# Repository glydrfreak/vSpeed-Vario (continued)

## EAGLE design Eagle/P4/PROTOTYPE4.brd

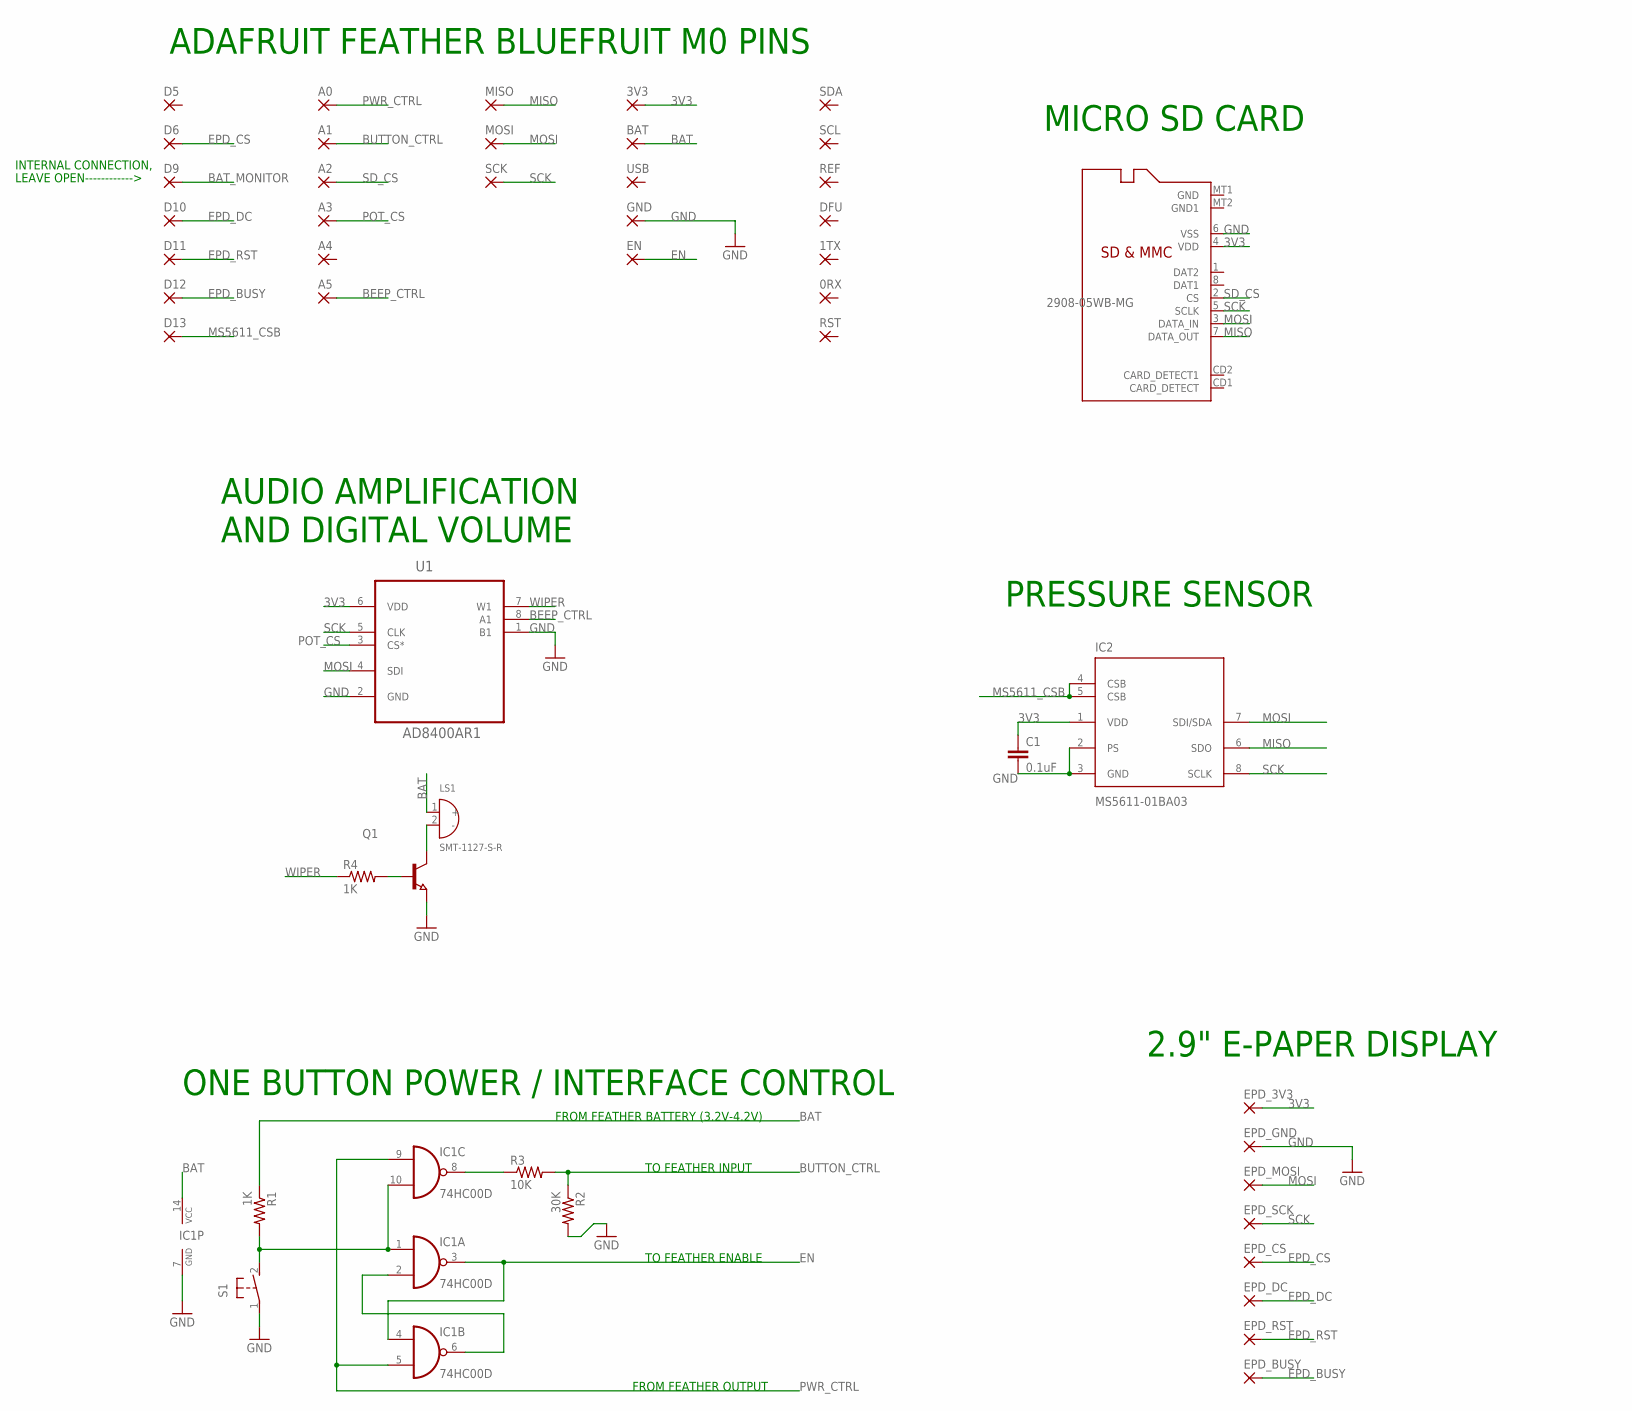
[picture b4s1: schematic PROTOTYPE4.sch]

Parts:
0RX, 1TX, 3V3: SMD2; SMD1,27-2,54
A0, A1, A2, A3, A4, A5: SMD2; SMD1,27-2,54
BAT: SMD2; SMD1,27-2,54
C1: 0.1uF; C0805K
D5, D6, D9, D10, D11, D12, D13: SMD2; SMD1,27-2,54
DFU: SMD2; SMD1,27-2,54
EN: SMD2; SMD1,27-2,54
EPD_3V3: SMD2; SMD1,27-2,54
EPD_BUSY: SMD2; SMD1,27-2,54
EPD_CS: SMD2; SMD1,27-2,54
EPD_DC: SMD2; SMD1,27-2,54
EPD_GND: SMD2; SMD1,27-2,54
EPD_MOSI: SMD2; SMD1,27-2,54
EPD_RST: SMD2; SMD1,27-2,54
EPD_SCK: SMD2; SMD1,27-2,54
GND: SMD2; SMD1,27-2,54
IC1: 74HC00D; SO14
IC2: MS5611-01BA03; SON125P300X500X100-8N
LS1: SMT-1127-S-R; XDCR_SMT-1127-S-R
MISO: SMD2; SMD1,27-2,54
MOSI: SMD2; SMD1,27-2,54
Q1: NPN-TRANSISTOR_SOT23; SOT23
R1, R4: 1K; R0805
R2: 30K; R0805
R3: 10K; R0805
REF: SMD2; SMD1,27-2,54
RST: SMD2; SMD1,27-2,54
S1: 31-XX; B3F-31XX; MPN B3F-3120
SCK: SMD2; SMD1,27-2,54
SCL: SMD2; SMD1,27-2,54
SDA: SMD2; SMD1,27-2,54
U1: AD8400AR1; SOIC127P600X175-8N
U$1: 2908-05WB-MG; MICROSD
USB: SMD2; SMD1,27-2,54

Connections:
3V3: 3V3.1, C1.1, EPD_3V3.1, IC2.1 (VDD), U1.6 (VDD), U$1.4 (VDD)
BAT: BAT.1, IC1.14 (VCC), LS1.1 (+), R1.1
BAT_MONITOR: D9.1
BEEP_CTRL: A5.1, U1.8 (A1)
BUTTON_CTRL: A1.1, R2.1, R3.2
EN: EN.1, IC1.3 (O), IC1.4 (I0)
EPD_BUSY: D12.1, EPD_BUSY.1
EPD_CS: D6.1, EPD_CS.1
EPD_DC: D10.1, EPD_DC.1
EPD_RST: D11.1, EPD_RST.1
GND: C1.2, EPD_GND.1, GND.1, IC1.7 (GND), IC2.2 (PS), IC2.3 (GND), Q1.2 (E), R2.2, S1.1, U1.1 (B1), U1.2 (GND), U$1.6 (VSS)
MISO: IC2.6 (SDO), MISO.1, U$1.7 (DATA_OUT)
MOSI: EPD_MOSI.1, IC2.7 (SDI/SDA), MOSI.1, U1.4 (SDI), U$1.3 (DATA_IN)
MS5611_CSB: D13.1, IC2.4 (CSB), IC2.5 (CSB)
unnamed: IC1.1 (I0), IC1.10 (I1), R1.2, S1.2 (S)
unnamed: IC1.2 (I1), IC1.6 (O)
unnamed: IC1.8 (O), R3.1
unnamed: Q1.1 (B), R4.2
unnamed: LS1.2 (-), Q1.3 (C)
POT_CS: A3.1, U1.3 (CS*)
PWR_CTRL: A0.1, IC1.5 (I1), IC1.9 (I0)
SCK: EPD_SCK.1, IC2.8 (SCLK), SCK.1, U1.5 (CLK), U$1.5 (SCLK)
SD_CS: A2.1, U$1.2 (CS)
WIPER: R4.1, U1.7 (W1)

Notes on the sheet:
TO FEATHER INPUT
TO FEATHER ENABLE
FROM FEATHER OUTPUT
FROM FEATHER BATTERY (3.2V-4.2V)
ADAFRUIT FEATHER BLUEFRUIT M0 PINS
ONE BUTTON POWER / INTERFACE CONTROL
MICRO SD CARD
PRESSURE SENSOR
AUDIO AMPLIFICATION AND DIGITAL VOLUME
2.9" E-PAPER DISPLAY
LEAVE OPEN------------>
INTERNAL CONNECTION,

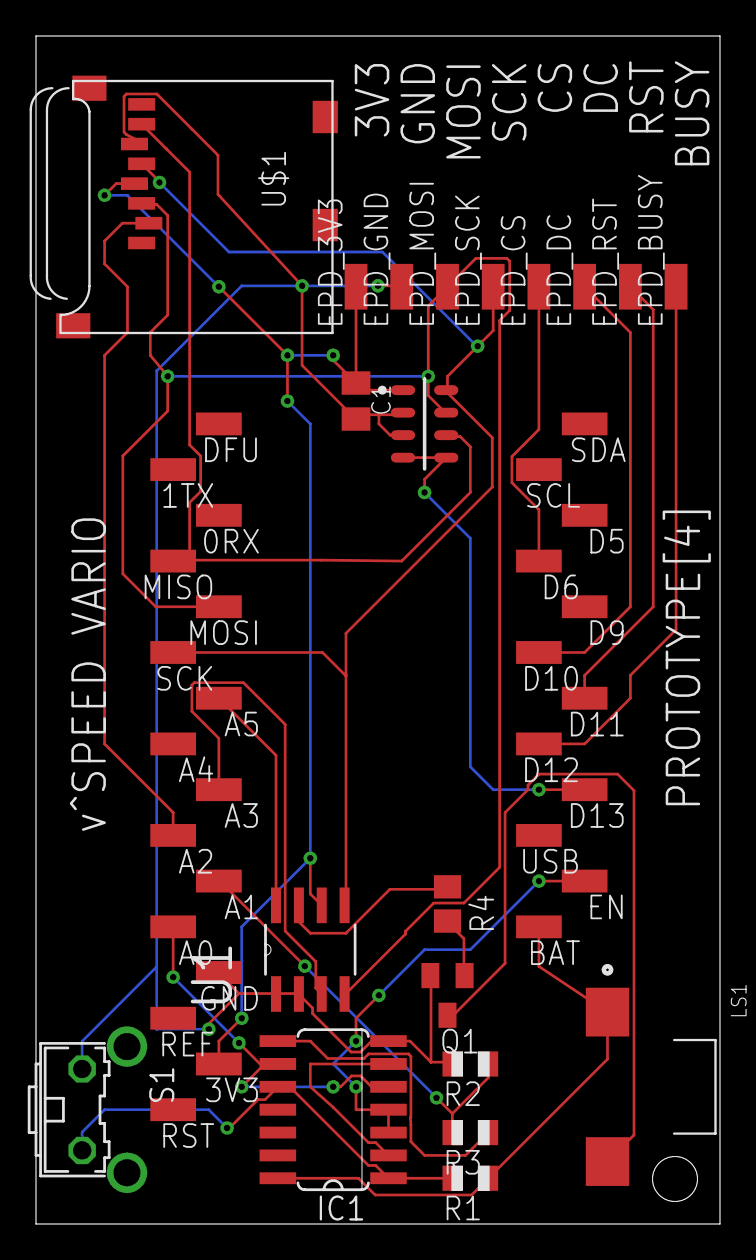
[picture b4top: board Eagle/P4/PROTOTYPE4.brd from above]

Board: 2 copper layers, 38.0 x 66.0 mm, 48 parts (0 on the bottom side), 23 nets.

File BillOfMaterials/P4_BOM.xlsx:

| PROTOTYPE[4]
 | Designator | Manufacturer Part Number | QTY | DESCRIPTION |  | DISTRIBUTER | DIVIDED PRICE | INCLUDED |  | DISTRIBUTER | DIVIDED PRICE | INCLUDED |  |  | DISTRIBUTER | EXTENDED PRICE | INCLUDED
 | R2 | RC0805FR-0730KL | 1 | RES 30K |  | DIGIKEY | 0.1 | 1 |  | DIGIKEY | 2.1999999999999999E-2 | 10 |  |  | DIGIKEY | 0.88 | 100
 | IC1 | 74HC00D,652 | 1 | NAND |  | DIGIKEY | 0.36 | 1 |  | DIGIKEY | 0.28999999999999998 | 10 |  |  | DIGIKEY | 19.739999999999998 | 100
 | C1 | 08055C104JAT2A | 1 | CAP 0.1UF |  | DIGIKEY | 0.1 | 1 |  | DIGIKEY | 7.0000000000000007E-2 | 10 |  |  | DIGIKEY | 3.1 | 100
 | R3 | RC0805JR-0710KL | 1 | RES 10K |  | DIGIKEY | 0.1 | 1 |  | DIGIKEY | 1.9E-2 | 10 |  |  | DIGIKEY | 0.76 | 100
 | R1,R4 | RC0805JR-071KL | 2 | RES 1K |  | DIGIKEY | 0.19 | 10 |  | DIGIKEY | 1.9E-2 | 20 |  |  | DIGIKEY | 1.52 | 200
 | U$1 | 2908-05WB-MG | 1 | SD |  | DIGIKEY | 3.6 | 1 |  | DIGIKEY | 3.4580000000000002 | 10 |  |  | DIGIKEY | 288.2 | 100
 | U1 | AD8400ARZ1 | 1 | SPI POT 1K |  | DIGIKEY | 3.31 | 1 |  | DIGIKEY | 3.31 | 10 |  |  | DIGIKEY | 281.255 | 100
 | Q1 | MMBT2222ALT1G | 1 | NPN TRANSISTOR |  | DIGIKEY | 0.12 | 1 |  | DIGIKEY | 0.106 | 10 |  |  | DIGIKEY | 5.75 | 100
 | S1 | B3F-3120 | 1 | BUTTON |  | DIGIKEY | 0.44 | 1 |  | DIGIKEY | 0.42399999999999999 | 10 |  |  | DIGIKEY | 34.520000000000003 | 100
 | DFU,MOSI,A3,GND,SDA,D9,D13 | 878980426 | 7 | VERT HEADER |  | DIGIKEY | 2.5300000000000002 | 10 |  | DIGIKEY | 1.77 | 100 |  |  | DIGIKEY | 106.134 | 700
 | EPD_3V3 | GEC08SBSN-M89 | 1 | RA HEADER |  | DIGIKEY | 1.53 | 1 |  | DIGIKEY | 1.367 | 10 |  |  | DIGIKEY | 112.6 | 100
 |  | ESTIMATED DIGIKEY SHIPPING | 1 | SHIPPING |  | SHIPPING | 3.69 | 1 |  | SHIPPING | 0.36899999999999999 | 10 |  |  | SHIPPING | 3.69 | 100
 | IC2 | MS561101BA03-50 | 1 | SENSOR |  | EBAY | 5.58 | 1 |  | EBAY | 5.58 | 10 |  |  | EBAY | 558 | 100
 | LS1 | BOT-03D-BUJEON, SMT-1127-S-R (ALT) | 1 | BUZZER |  | EBAY | 3.61 | 10 |  | EBAY | 0.36099999999999999 | 10 |  |  | EBAY | 36.1 | 100
 |  | 2.9 INCH E-PAPER MODULE WITH WIRES | 1 | EPAPER |  | EBAY | 18.760000000000002 | 1 |  | EBAY | 18.752000000000002 | 10 |  |  | EBAY | 1875.2 | 100
 |  | SOLDER PASTE | ? | SOLDER PASTE |  | EBAY | UNKNOWN |  |  | EBAY | UNKNOWN |  |  |  | EBAY | UNKNOWN
 |  | ESTIMATED EBAY SHIPPING | 1 | SHIPPING |  | SHIPPING | 3.18 | 1 |  | SHIPPING | 1.2310000000000001 | 10 |  |  | SHIPPING | 113.85000000000001 | 100
 |  | BLUEFRUIT FEATHER M0 | 1 | CONTROLLER |  | ADAFRUIT | 29.95 | 1 |  | ADAFRUIT | 26.96 | 10 |  |  | ADAFRUIT | 2396 | 100
 |  | FEMALE HEADER SOCKETS 12 AND 16 PIN | 1 | SOCKET |  | ADAFRUIT | 0.95 | 1 |  | ADAFRUIT | 0.86 | 10 |  |  | ADAFRUIT | 76 | 100
 |  | ADAFRUIT SHIPPING | 1 | SHIPPING |  | SHIPPING | 4.05 | 1 |  | ADAFRUIT | FREE | 10 |  |  | ADAFRUIT | FREE | 100
 |  | BTG 150mAh LIPO BATTERY | 1 | BATTERY |  | AMAZON | 12.85 | 5 |  | AMAZON | 2.57 | 10 |  |  | AMAZON | 257 | 100
 |  | FREE SHIPPING WITH AMAZON PRIME | 1 | SHIPPING |  | SHIPPING | FREE | 5 |  | SHIPPING | FREE | 10 |  |  | SHIPPING | FREE | 100
 |  | PCB | 1 | EAGLE CAD |  | SEEED | 4.9000000000000004 | 5 |  | SEEED | 0.49000000000000005 | 10 |  |  | SEEED | 41.59 | 100
 |  | SEEED STUDIO SHIPPING | 1 | SHIPPING |  | SHIPPING | 10.85 | 5 |  | SEEED | 1.1139999999999999 | 10 |  |  | SEEED | 17.55 | 100
 |  | SOLDER STENCIL | 1 | HOME 3D PRINTED |  | PRUSA MK3 | UNKNOWN | 1 |  | PRUSA MK3 | UNKNOWN | 10 |  |  | PRUSA MK3 | UNKNOWN | 100
 |  | CASE (THREE PIECES TOTAL) | 1 | HOME 3D PRINTED |  | PRUSA MK3 | UNKNOWN | 1 |  | PRUSA MK3 | UNKNOWN | 10 |  |  | PRUSA MK3 | UNKNOWN | 100
 |  | ASSUMING YOU HAVE YOUR OWN PRINTER | 1 | SHIPPING |  | SHIPPING | FREE |  |  | SHIPPING | FREE |  |  |  | SHIPPING | FREE
 |  |  |  |  |  | TOTAL PURCHASE | 110.74999999999999 |  |  | TOTAL PURCHASE | 691.42 |  |  |  | TOTAL PURCHASE | 6229.4389999999994
 |  |  |  |  |  | 1 VARIO | 110.74999999999999 | EACH |  | 10 VARIOS | 69.141999999999996 | EACH |  |  | 100 VARIOS | 62.294389999999993 | EACH

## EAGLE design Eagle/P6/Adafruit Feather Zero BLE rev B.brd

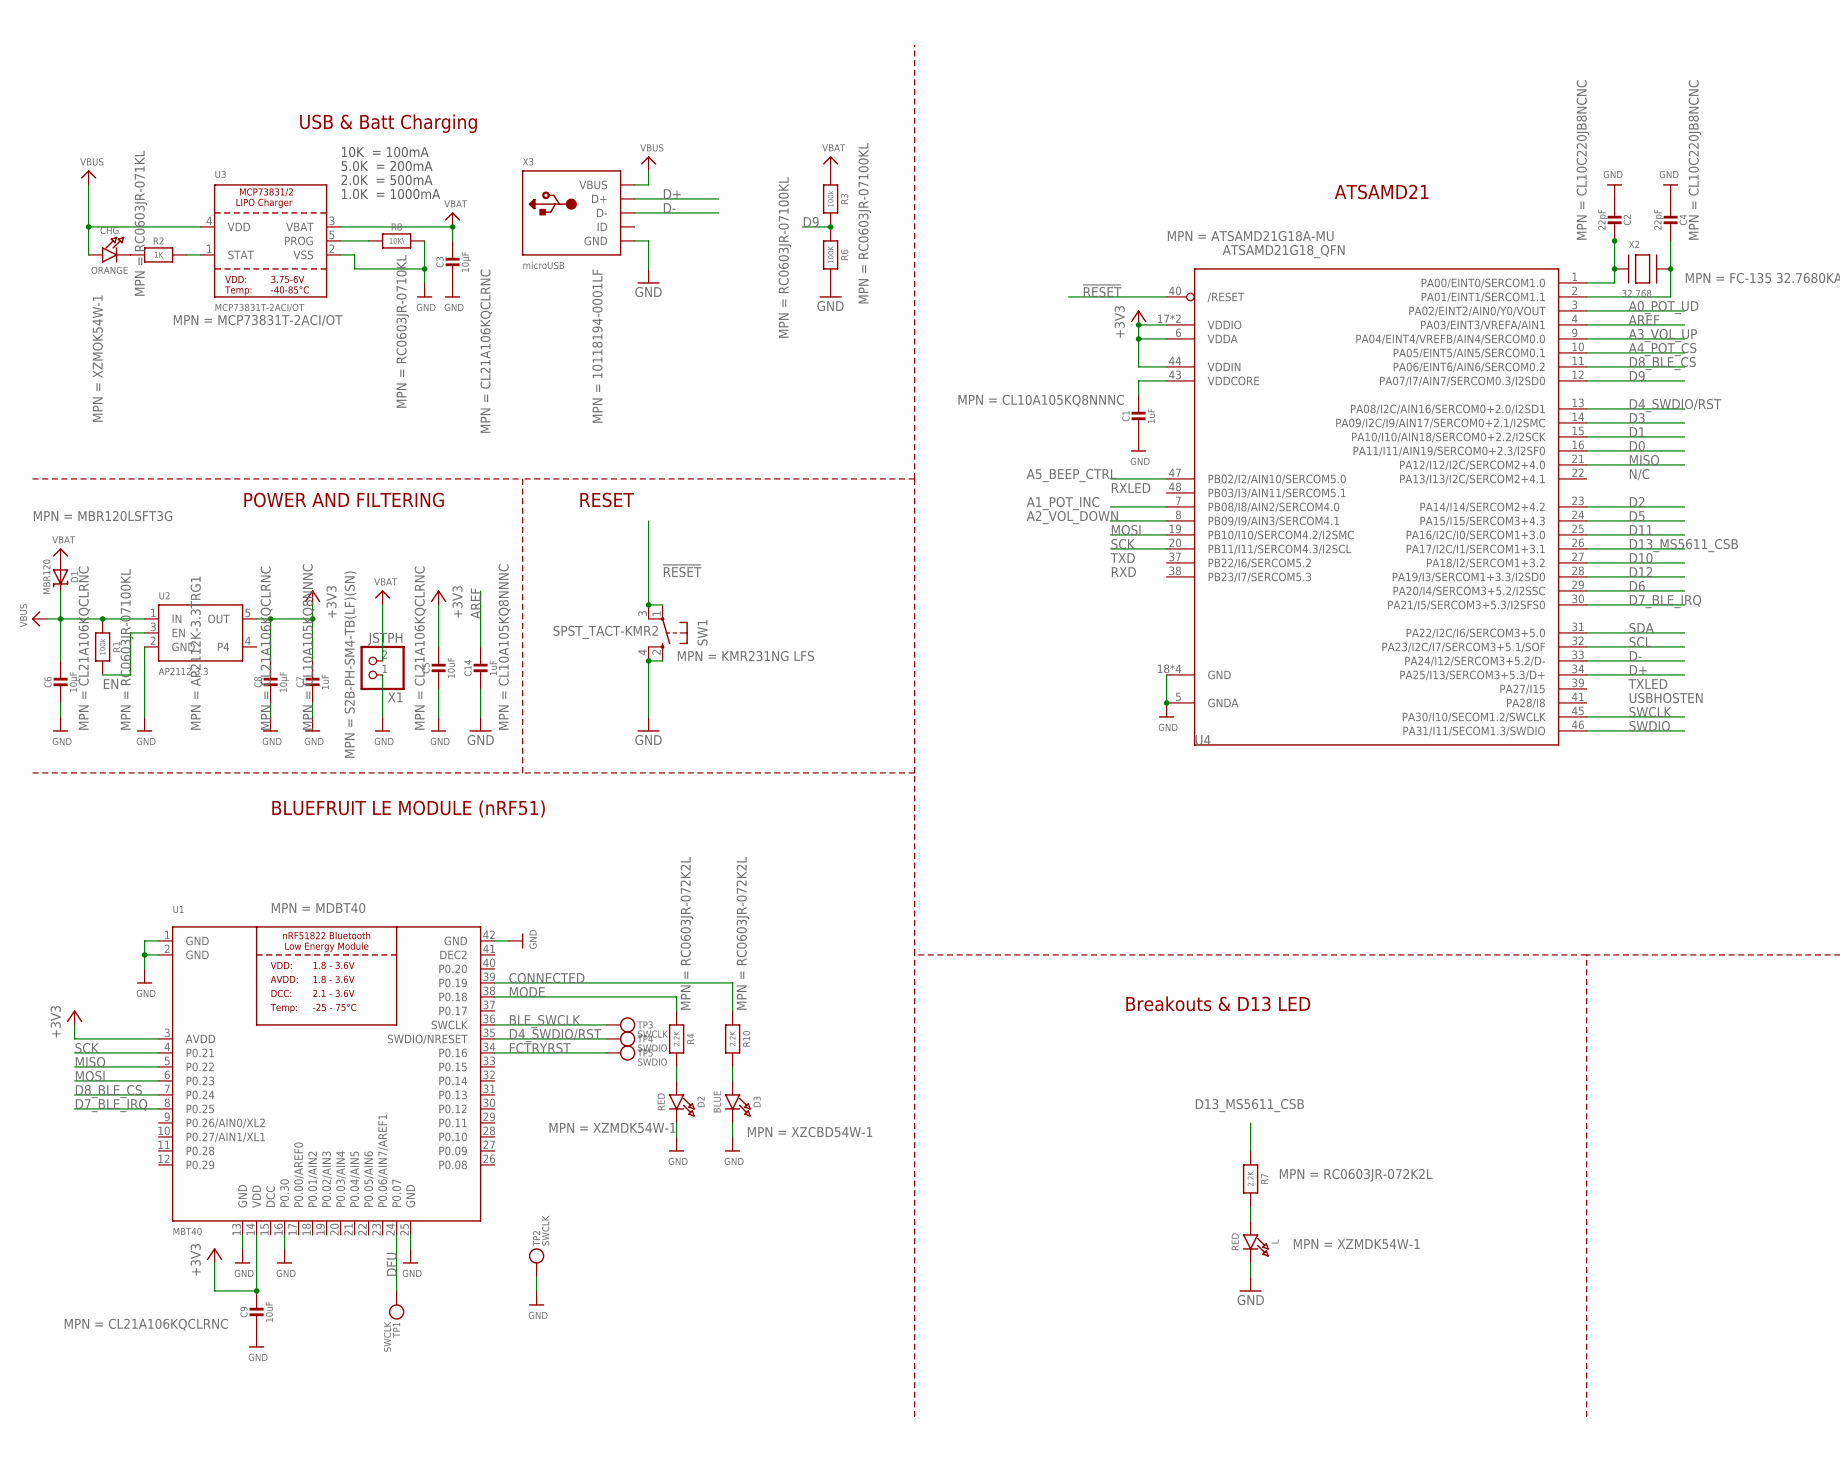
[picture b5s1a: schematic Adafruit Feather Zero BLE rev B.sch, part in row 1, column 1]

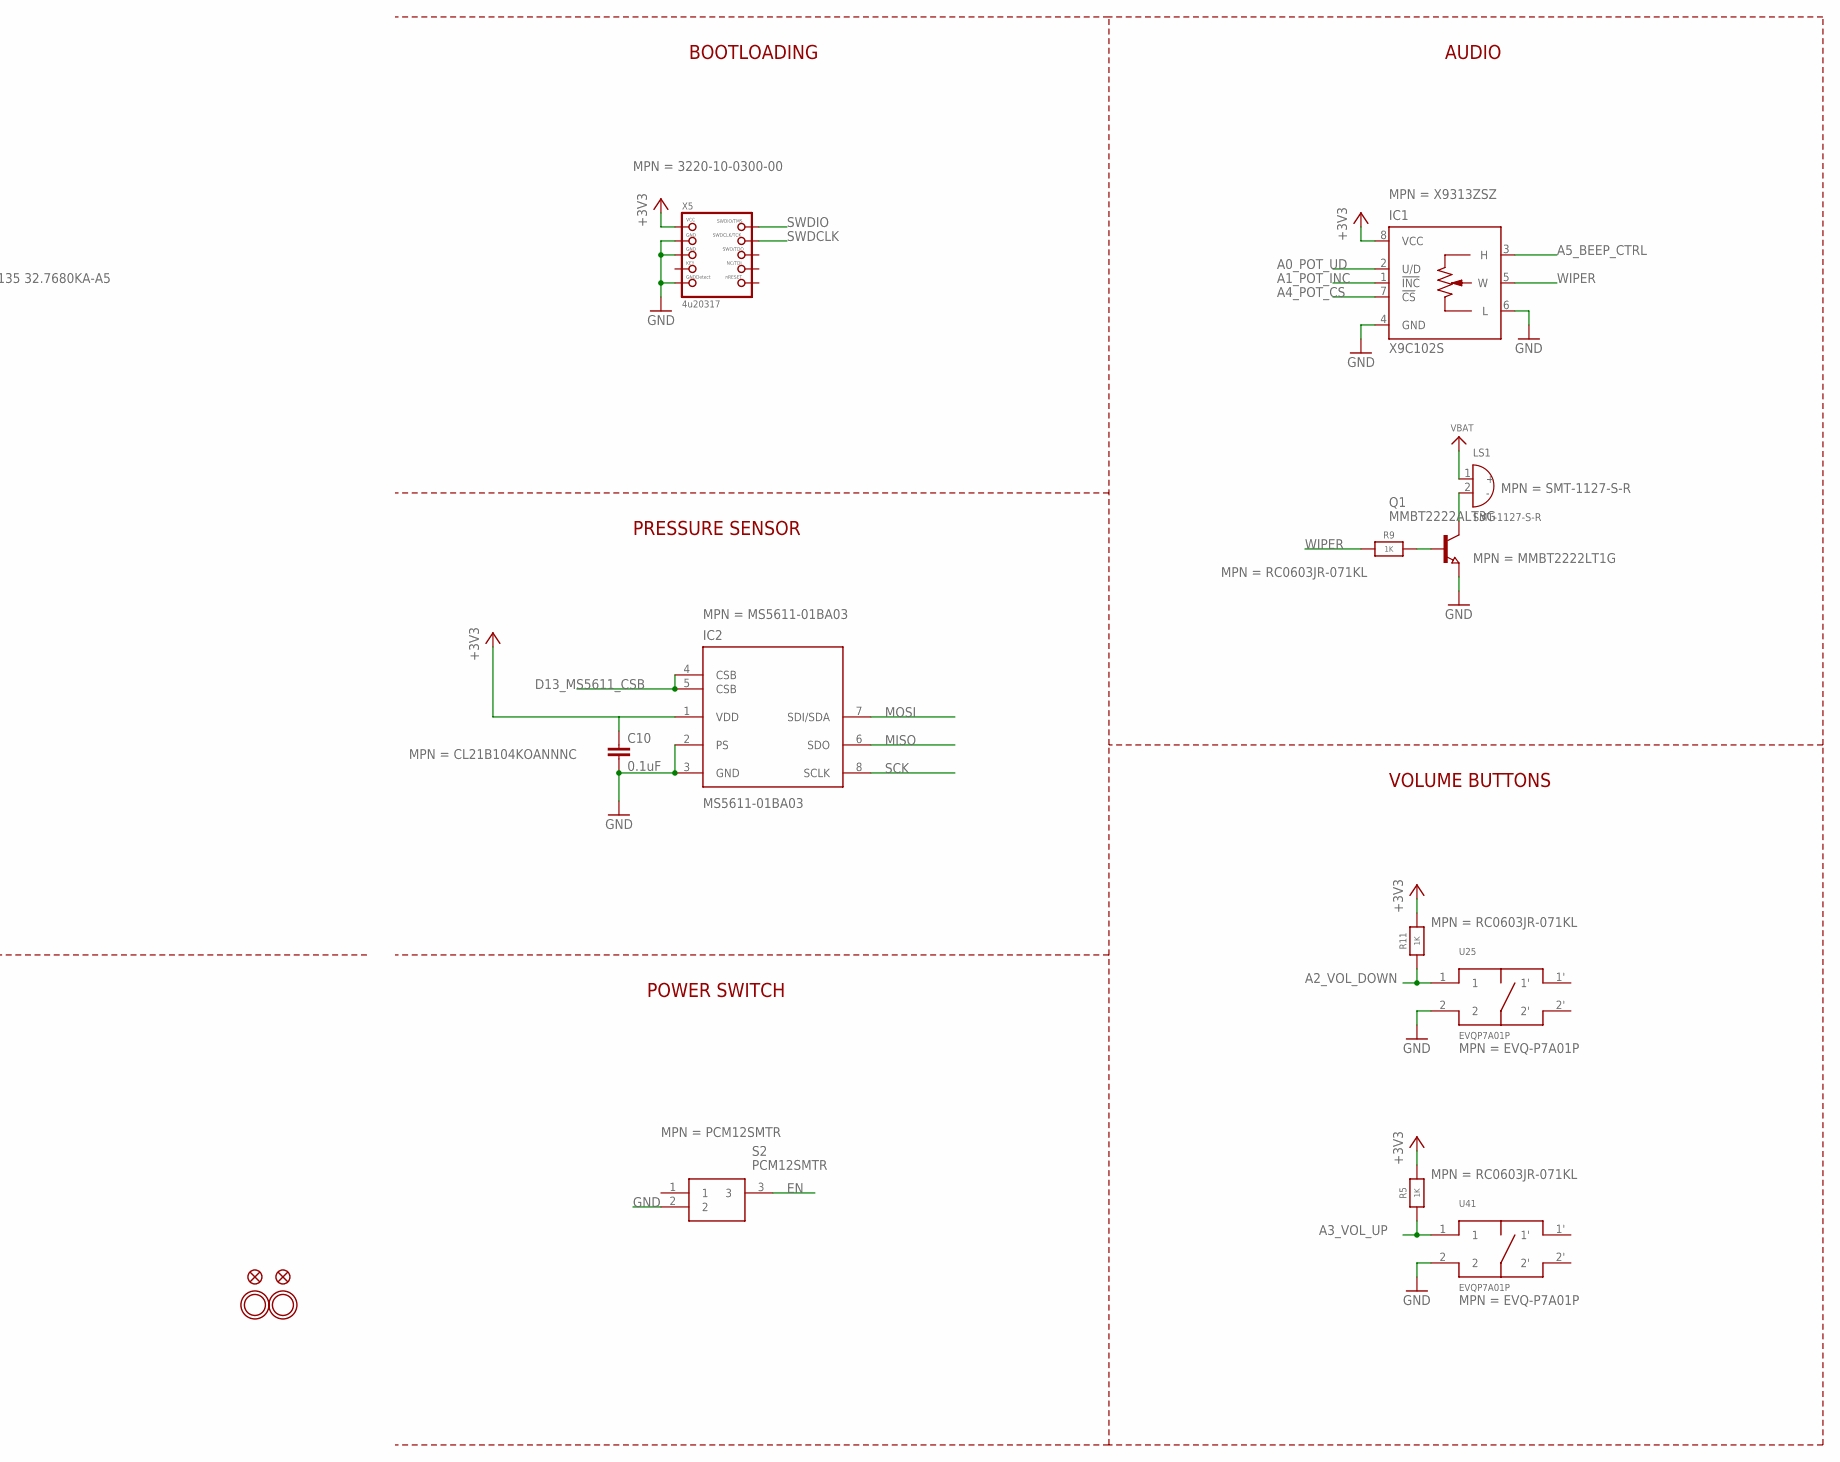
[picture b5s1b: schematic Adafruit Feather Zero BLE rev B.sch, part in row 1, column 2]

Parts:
C1, C7, C14: 1uF; 0603-NO; MPN CL10A105KQ8NNNC
C2, C4: 22pF; 0603-NO; MPN CL10C220JB8NCNC
C3, C6, C8: 10µF; 0805-NO; MPN CL21A106KQCLRNC
C5, C9: 10uF; 0805-NO; MPN CL21A106KQCLRNC
C10: 0.1uF; C0805K; MPN CL21B104KOANNNC
CHG: ORANGE; CHIPLED_0805_NOOUTLINE; MPN XZMOK54W-1
D1: MBR120; SOD-123; MPN MBR120LSFT3G
D2: RED; CHIPLED_0805_NOOUTLINE; MPN XZMDK54W-1
D3: BLUE; CHIPLED_0805_NOOUTLINE; MPN XZCBD54W-1
IC1: X9C102S; SOIC08; MPN X9313ZSZ
IC2: MS5611-01BA03; SON125P300X500X100-8N; MPN MS5611-01BA03
L: RED; CHIPLED_0805_NOOUTLINE; MPN XZMDK54W-1
LS1: SMT-1127-S-R; XDCR_SMT-1127-S-R; MPN SMT-1127-S-R
Q1: MMBT2222ALT3G; SOT23; MPN MMBT2222LT1G
R1, R3: 100k; 0603-NO; MPN RC0603JR-07100KL
R2, R5, R9, R11: 1K; 0603-NO; MPN RC0603JR-071KL
R4, R7, R10: 2.2K; 0603-NO; MPN RC0603JR-072K2L
R6: 100K; 0603-NO; MPN RC0603JR-07100KL
R8: 10K\; 0603-NO; MPN RC0603JR-0710KL
S2: PCM12SMTR; PCM12SMTR_1; MPN PCM12SMTR
SW1: SPST_TACT-KMR2; KMR2; MPN KMR231NG LFS
TP1, TP2, TP3: SWCLK; PAD-1.5X2.0
TP4, TP5: SWDIO; PAD-1.5X2.0
U1: MBT40; BLE_MODULE_RAYTAC_MDBT40; MPN MDBT40
U2: AP2112-3.3; SOT23-5; MPN AP2112K-3.3TRG1
U3: MCP73831T-2ACI/OT; SOT23-5; MPN MCP73831T-2ACI/OT
U4: ATSAMD21G18_QFN; TQFN48_7MM; MPN ATSAMD21G18A-MU
U25, U41: EVQP7A01P; MPN EVQ-P7A01P
U$31, U$32: MOUNTINGHOLE2.5; MOUNTINGHOLE_2.5_PLATED
U$34, U$35: FIDUCIAL""; FIDUCIAL_1MM
X1: JSTPH; JSTPH2; MPN S2B-PH-SM4-TB(LF)(SN)
X2: 32.768; XTAL3215; MPN FC-135 32.7680KA-A5
X3: microUSB; 4UCONN_20329_V2; MPN 10118194-0001LF
X5: 4u20317; 2X05_1.27MM_BOX_POSTS; MPN 3220-10-0300-00

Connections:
!RESET: SW1.1, SW1.3 (P1), U4.40 (/RESET); also elsewhere on the board
+3V3: C5.1, C7.1, C8.1, C9.1, C10.1, IC1.8 (VCC), IC2.1 (VDD), R5.2, R11.2, U1.3 (AVDD), U1.14 (VDD), U2.5 (OUT), U4.6 (VDDA), U4.17 (VDDIO), U4.44 (VDDIN), X5.1 (VCC); also elsewhere on the board
A0_POT_UD: IC1.2 (U/D), U4.3 (PA02/EINT2/AIN0/Y0/VOUT); also elsewhere on the board
A1_POT_INC: IC1.1 (!INC), U4.7 (PB08/I8/AIN2/SERCOM4.0); also elsewhere on the board
A2_VOL_DOWN: R11.1, U4.8 (PB09/I9/AIN3/SERCOM4.1), U25.1; also elsewhere on the board
A3_VOL_UP: R5.1, U4.9 (PA04/EINT4/VREFB/AIN4/SERCOM0.0), U41.1; also elsewhere on the board
A4_POT_CS: IC1.7 (!CS), U4.10 (PA05/EINT5/AIN5/SERCOM0.1); also elsewhere on the board
A5_BEEP_CTRL: IC1.3 (H), U4.47 (PB02/I2/AIN10/SERCOM5.0); also elsewhere on the board
AREF: C14.1, U4.4 (PA03/EINT3/VREFA/AIN1); also elsewhere on the board
BLE_SWCLK: TP3.P$1, U1.36 (SWCLK)
CONNECTED: R10.1, U1.39 (P0.19)
D4_SWDIO/RST: TP4.P$1, U1.35 (SWDIO/NRESET), U4.13 (PA08/I2C/AIN16/SERCOM0+2.0/I2SD1); also elsewhere on the board
D7_BLE_IRQ: U1.8 (P0.25), U4.30 (PA21/I5/SERCOM3+5.3/I2SFS0); also elsewhere on the board
D8_BLE_CS: U1.7 (P0.24), U4.11 (PA06/EINT6/AIN6/SERCOM0.2); also elsewhere on the board
D9: R3.2, R6.1, U4.12 (PA07/I7/AIN7/SERCOM0.3/I2SD0); also elsewhere on the board
D13_MS5611_CSB: IC2.4 (CSB), IC2.5 (CSB), R7.1, U4.26 (PA17/I2C/I1/SERCOM1+3.1); also elsewhere on the board
D+: U4.34 (PA25/I13/SERCOM3+5.3/D+), X3.D+; also elsewhere on the board
D-: U4.33 (PA24/I12/SERCOM3+5.2/D-), X3.D-; also elsewhere on the board
DCC: U1.15 (DCC)
DEC2: U1.41 (DEC2)
DFU: TP1.P$1, U1.24 (P0.07)
EN: R1.2, S2.3, U2.3 (EN); also elsewhere on the board
FCTRYRST: TP5.P$1, U1.34 (P0.16)
GND: C1.2, C2.2, C3.2, C4.2, C5.2, C6.2, C7.2, C8.2, C9.2, C10.2, C14.2, D2.C, D3.C, IC1.4 (GND), IC1.6 (L), IC2.2 (PS), IC2.3 (GND), L.C, Q1.2 (E), R6.2, R8.2, S2.2, SW1.2 (S), SW1.4 (S1), TP2.P$1, U1.1 (GND), U1.2 (GND), U1.13 (GND), U1.16 (P0.30), U1.25 (GND), U1.42 (GND), U2.2 (GND), U3.2 (VSS), U4.5 (GNDA), U4.18 (GND), U25.2, U41.2, X1.1, X3.BASE@1 (GND), X3.BASE@2 (GND), X3.GND, X3.SPRT@1 (GND), X3.SPRT@2 (GND), X3.SPRT@3 (GND), X3.SPRT@4 (GND), X5.3 (GND), X5.5 (GND), X5.9 (GNDDETECT); also elsewhere on the board
MISO: IC2.6 (SDO), U1.5 (P0.22), U4.21 (PA12/I12/I2C/SERCOM2+4.0); also elsewhere on the board
MODE: R4.1, U1.38 (P0.18)
MOSI: IC2.7 (SDI/SDA), U1.6 (P0.23), U4.19 (PB10/I10/SERCOM4.2/I2SMC); also elsewhere on the board
unnamed: CHG.C, R2.1
unnamed: L.A, R7.2
unnamed: R2.2, U3.1 (STAT)
unnamed: R8.1, U3.5 (PROG)
unnamed 40: C2.1, U4.1 (PA00/EINT0/SERCOM1.0), X2.P$1; also elsewhere on the board
unnamed: D2.A, R4.2
unnamed 42: C4.1, U4.2 (PA01/EINT1/SERCOM1.1), X2.P$2; also elsewhere on the board
unnamed: D3.A, R10.2
unnamed: Q1.1 (B), R9.2
unnamed: LS1.2 (-), Q1.3 (C)
SCK: IC2.8 (SCLK), U1.4 (P0.21), U4.20 (PB11/I11/SERCOM4.3/I2SCL); also elsewhere on the board
SWDCLK: X5.4 (SWDCLK)
SWDIO: U4.46 (PA31/I11/SECOM1.3/SWDIO), X5.2 (SWDIO); also elsewhere on the board
VBAT: C3.1, D1.A, LS1.1 (+), R3.1, U3.3 (VBAT), X1.2; also elsewhere on the board
VBUS: C6.1, CHG.A, D1.C, R1.1, U2.1 (IN), U3.4 (VDD), X3.VBUS
VDDCORE: C1.1, U4.43 (VDDCORE); also elsewhere on the board
WIPER: IC1.5 (W), R9.1

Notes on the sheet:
POWER AND FILTERING
RESET
10K = 100mA
5.0K = 200mA
2.0K = 500mA
1.0K = 1000mA
N/C
TXLED
USBHOSTEN
RXLED
TXD
RXD
BLUEFRUIT LE MODULE (nRF51)
ATSAMD21
USB & Batt Charging
Breakouts & D13 LED
BOOTLOADING
PRESSURE SENSOR
AUDIO
POWER SWITCH
VOLUME BUTTONS

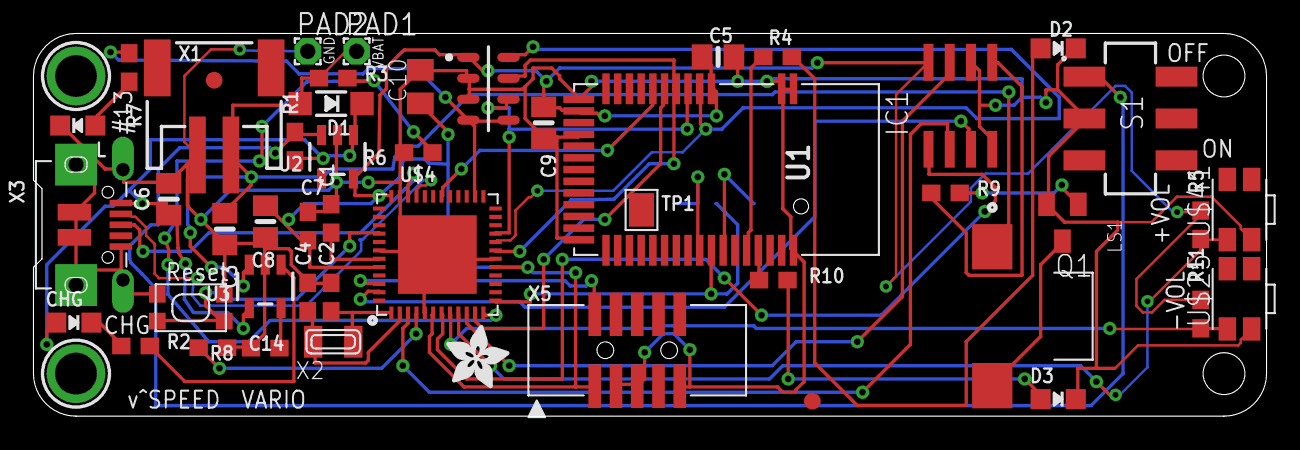
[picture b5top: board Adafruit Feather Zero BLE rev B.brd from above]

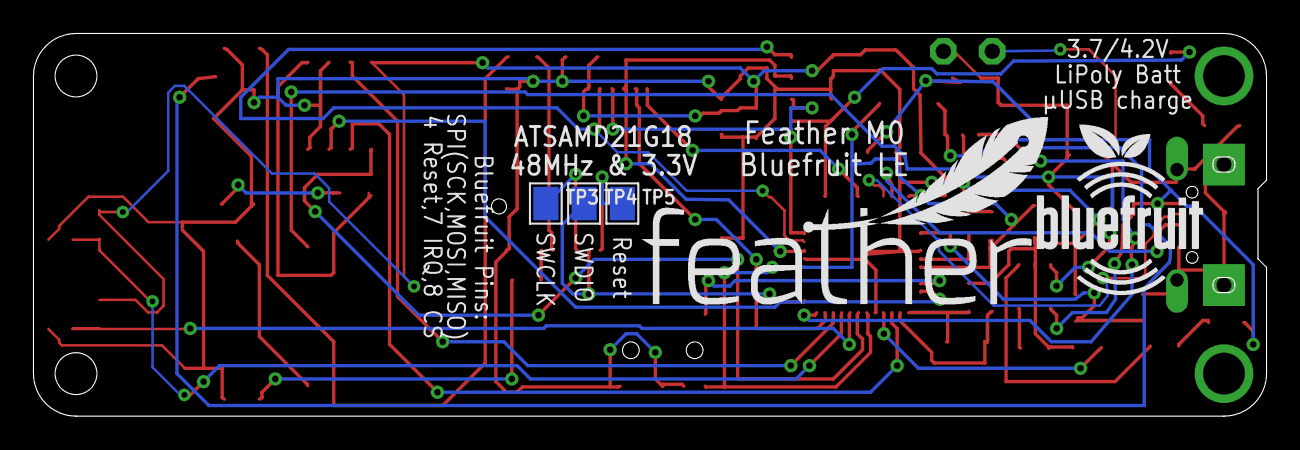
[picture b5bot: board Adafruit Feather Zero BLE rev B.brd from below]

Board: 2 copper layers, 73.7 x 22.9 mm, 56 parts (5 on the bottom side), 41 nets.

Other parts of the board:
PAD1, PAD2: WIREPAD1,6/0,9; 1,6/0,9
S1: JS202011SCQN
U$4: ATSAMD21G18_QFN; TQFN48_7MM
U$7: ADAFRUIT_3.5MM
U$9: FEATHERLOGO
U$25, U$41: EVQP7A01P
U$26: BLUEFRUITLOGO_100MM

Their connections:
!RESET: U$4.40; also elsewhere on the board
+3V3: U$4.6, U$4.17, U$4.36, U$4.44; also elsewhere on the board
A0_POT_UD: U$4.3; also elsewhere on the board
A1_POT_INC: U$4.7; also elsewhere on the board
A2_VOL_DOWN: U$4.8, U$25.1; also elsewhere on the board
A3_VOL_UP: U$4.9, U$41.1; also elsewhere on the board
A4_POT_CS: U$4.10; also elsewhere on the board
A5_BEEP_CTRL: U$4.47; also elsewhere on the board
AREF: U$4.4; also elsewhere on the board
D4_SWDIO/RST: U$4.13; also elsewhere on the board
D7_BLE_IRQ: U$4.30; also elsewhere on the board
D8_BLE_CS: U$4.11; also elsewhere on the board
D9: U$4.12; also elsewhere on the board
D13_MS5611_CSB: U$4.26; also elsewhere on the board
D+: U$4.34; also elsewhere on the board
D-: U$4.33; also elsewhere on the board
EN: S1.1; also elsewhere on the board
GND: PAD2.1, S1.2, U$4.5, U$4.18, U$4.35, U$4.42, U$4.THERMAL, U$25.2, U$41.2; also elsewhere on the board
MISO: U$4.21; also elsewhere on the board
MOSI: U$4.19; also elsewhere on the board
unnamed 40: U$4.1; also elsewhere on the board
unnamed 42: U$4.2; also elsewhere on the board
SCK: U$4.20; also elsewhere on the board
SWDIO: U$4.46; also elsewhere on the board
VBAT: PAD1.1; also elsewhere on the board
VDDCORE: U$4.43; also elsewhere on the board

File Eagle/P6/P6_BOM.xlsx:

INSTOCK | REQUIRED QTY | PRICE BREAKS | Parts | MPN | DESCRIPTION | DISTRIBUTER | PRICE @ QTY 1 VARIO | PRICE @ QTY 10 VARIOS
0 | 1 | 1, 10 | Q1 | MMBT2222LT1G | NPN SOT23 | DIGIKEY | 0.13 | 0.115
9 | 1 | 1, 10 | C10 | CL21B104KOANNNC | CAP 0.1uF 0805 | DIGIKEY | 0.1 | 2.9000000000000001E-2
0 | 3 | 10, 100 | R1, R3, R6 | RC0603JR-07100KL | RES 100K 0603 | DIGIKEY | 1.0999999999999999E-2 | 4.5999999999999999E-3
0 | 1 | 1, 10 | R8 | RC0603JR-0710KL | RES 10K 0603 | DIGIKEY | 0.1 | 1.0999999999999999E-2
0 | 5 | 10, 100 | C3, C5, C6, C8, C9 | CL21A106KQCLRNC | CAP 10uF 0805 | DIGIKEY | 7.0000000000000007E-2 | 3.1300000000000001E-2
0 | 2 | 10, 100 | R2, R9 | RC0603JR-071KL | RES 1K 0603 | DIGIKEY | 1.0999999999999999E-2 | 4.5999999999999999E-3
0 | 3 | 10, 100 | C1, C7, C14 | CL10A105KQ8NNNC | CAP 1uF 0603 | DIGIKEY | 3.2000000000000001E-2 | 1.43E-2
0 | 3 | 10, 100 | R4, R7, R10 | RC0603JR-072K2L | RES 2.2K 0603 | DIGIKEY | 1.0999999999999999E-2 | 4.5999999999999999E-3
0 | 2 | 10, 100 | C2, C4 | CL10C220JB8NCNC | CAP 22pF 0603 | DIGIKEY | 3.2000000000000001E-2 | 1.43E-2
0 | 1 | 10, 10 | X2 | XTAL3215 | CRYSTAL 32.768KHz | EBAY | 2.16 | 2.16
0 | 1 | 1, 10 | X5 | 3220-10-0300-00 | SWD 10PIN CONNECTOR | DIGIKEY | 0.61 | 0.56999999999999995
0 | 1 | 1, 10 | U2 | AP2112K-3.3TRG1 | VOLTAGE REGULATOR | DIGIKEY | 0.48 | 0.36199999999999999
0 | 1 | 1, 25 | U$4 | ATSAMD21G18A-MU | ATSAMD21G18_QFN | DIGIKEY | 3.18 | 2.8832
0 | 1 | 1, 10 | D3 | XZCBD54W-1 | LED BLUE 0805 | DIGIKEY | 0.5 | 0.35599999999999998
0 | 1 | 1, 10 | S1 | JS202011SCQN | SLIDE SWITCH | DIGIKEY | 0.48 | 0.46300000000000002
1 | 1 | 1, 10 | X1 | S2B-PH-SM4-TB(LF)(SN) | JSTPH | DIGIKEY | 0.57999999999999996 | 0.54700000000000004
0 | 1 | 1, 10 | D1 | MBR120LSFT3G | DIODE | DIGIKEY | 0.43 | 0.32100000000000001
0 | 1 | 1, 10 | U1 | MDBT40 | NRF51822 BLE MODULE | EBAY | 10.5 | 6.5250000000000004
0 | 1 | 1, 25 | U3 | MCP73831T-2ACI/OT | LIPO CHARGER | DIGIKEY | 0.59 | 0.49840000000000001
0 | 1 | 1, 1 | IC2 | MS5611 | PRESSURE SENSOR | EBAY | 7.43 | 7.43
0 | 1 | 1, 10 | CHG | XZMOK54W-1 | LED ORANGE 0805 | DIGIKEY | 0.44 | 0.317
0 | 2 | 10, 25 | D2, L | XZMDK54W-1 | LED RED 0805 | DIGIKEY | 0.317 | 0.24279999999999999
13 | 1 | 1, 10 | LS1 | SMT-1127-S-R | SMT-1127-S-R | DIGIKEY | 2.27 | 2.0630000000000002
0 | 3 | 10, 50 | SW1, SW2, SW3 | KMR231NG LFS | TACT SWITCH | DIGIKEY | 0.499 | 0.47120000000000001
0 | 1 | 1, 10 | IC1 | X9313ZSZ | DIGIPOT 1K SOIC8 | DIGIKEY | 3.6 | 3.2370000000000001
0 | 1 | 1, 10 | X3 | 10118194-0001LF | microUSB | DIGIKEY | 0.46 | 0.437
0 | 1 | 10, 10 |  |  | PCB AND STENCIL | SEEED | 29.35 | 2.9350000000000001
 |  |  |  | 1570 | 100 mAh LIPO | DIGIKEY | 5.95 | 5.95
 |  |  |  |  |  |  | 70.323000000000008 | 37.997300000000003

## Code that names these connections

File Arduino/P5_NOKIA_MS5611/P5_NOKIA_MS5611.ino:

#include <SPI.h>
#include <Adafruit_GFX.h>
#include "Adafruit_PCD8544.h"
#include "MS5611.h"
#include "MS5611_I2C.h"
#include "FILTER.h"
#include "BEEP.h"


#define NOKIA_DC 10
#define NOKIA_CS 6
#define NOKIA_RST 11
#define NOKIA_LIGHT 12
Adafruit_PCD8544 display = Adafruit_PCD8544(NOKIA_DC, NOKIA_CS, NOKIA_RST);           //HARDWARE SPI
// Note with hardware SPI MISO and SS pins aren't used but will still be read
// and written to during SPI transfer.  Be careful sharing these pins!


#define MS5611_CSB                    13    // Chip/Slave Select Pin
#define D1_OSR                         5    // (Default pressure OSR mode 5) 
#define D2_OSR                         2    // (Default temperature OSR mode 2)
#define PRESSURE_FILTER_DURATION    1000    // (AVERAGING DURATION: 1ms to 2000ms)
#define ALTITUDE_FILTER_DURATION    1000    // (AVERAGING DURATION: 1ms to 2000ms)
#define VSPEED_FILTER_DURATION       750    // (AVERAGING DURATION: 1ms to 2000ms)
#define TEMPERATURE_FILTER_DURATION    0    // (AVERAGING DURATION: 1ms to 2000ms)
#define BEEP_PIN                      A5    // (Default A5) Pin connected to buzzer 
#define POT_CS                        A4
#define BUTTON_UP                     A0
#define BUTTON_SELECT                 A1
#define BUTTON_DOWN                   A2



MS5611_SPI MS5611;
MS5611_I2C MS5611_I2C; 
FILTER1 FILTER1;
FILTER2 FILTER2;
FILTER3 FILTER3;
FILTER4 FILTER4;
BEEP BEEP;


float temperatureF = 0;
float pressurePa = 0;
float altitudeFt = 0;
float velocityFtPerSec = 0;
unsigned long previousMillis = 0;
int samplesThisSec = 0;    // Used for calculating averaging duration
int samplesPerSec = 0;     // Used for displaying samplesPerSec updated every once second
int BRIGHTNESS = 0;   // 0% - 100%
int contrast = 0;
int volume = 55;
int volDelay = 100;   // Volume shall only be changed every 100ms;
unsigned long volMillis = 0;


void adjustVolumeTo(int volLevel);



void setup()   {

  pinMode(BUTTON_UP, INPUT_PULLUP);
  pinMode(BUTTON_DOWN, INPUT_PULLUP);
  pinMode(BUTTON_SELECT, INPUT_PULLUP);

  SPI.begin();
  pinMode(POT_CS, OUTPUT);
  digitalWrite(POT_CS, HIGH);
  adjustVolumeTo(volume);  // 55, 71, 102, 255

  
  pinMode(NOKIA_LIGHT, OUTPUT);
  analogWrite(NOKIA_LIGHT, map(BRIGHTNESS, 0,100, 255,0)); //0-255;
  
  Serial.begin(115200);

  display.begin();
  display.setContrast(contrast); //Default 100 in display.begin();

  display.display(); // show splashscreen
  delay(2000);
  display.clearDisplay();   // clears the screen and buffer

  //MS5611_I2C.begin();
  //MS5611_I2C.setOversampling(MS5611_HIGH_RES);
  MS5611.begin(MS5611_CSB);

}


void loop() {
  
  
  
  //int ANALOG_LIGHT = map(BRIGHTNESS, 0, 100, 255, 0);
  //analogWrite(NOKIA_LIGHT, ANALOG_LIGHT);
  
  samplesThisSec++; //increment each time the loop cycles
  if(millis() - previousMillis >= 1000){ // Update value of samplesPerSec once every second:
    previousMillis=millis();
    samplesPerSec = samplesThisSec;
    samplesThisSec=0; 
    //Serial.println(samplesPerSec);  //print debug info
    contrast += 10;
    display.setContrast(contrast);
  }

      //====MS5611=================================================================/
        
        //TEMPERATURE:
        if(TEMPERATURE_FILTER_DURATION){
          temperatureF = FILTER4.RUNNING_AVERAGE(
            //(MS5611_I2C.readTemperature()*9/5.0)+32,
            MS5611.getTemperatureF(D2_OSR), 
            samplesPerSec, 
            TEMPERATURE_FILTER_DURATION
          );
          //temperatureF = 77;
        }
        else{
          temperatureF = MS5611.getTemperatureF(D2_OSR);
          //temperatureF = (MS5611_I2C.readTemperature()*9/5.0)+32;
        }
        
        //PRESSURE:
        if(PRESSURE_FILTER_DURATION){
          pressurePa = FILTER1.RUNNING_AVERAGE(
            MS5611.getPressurePa(D1_OSR),  //WHY THE HECK IS THIS INVERTED ALL THE SUDDEN???
            //MS5611_I2C.readPressure(), 
            samplesPerSec, 
            PRESSURE_FILTER_DURATION
          );
        }
        else{
          pressurePa = MS5611.getPressurePa(D1_OSR);  //WHY THE HECK IS THIS INVERTED ALL THE SUDDEN???
          //pressurePa = MS5611_I2C.readPressure();
        }
        
        //ALTITUDE:
        if(ALTITUDE_FILTER_DURATION){
          altitudeFt = FILTER2.RUNNING_AVERAGE(
            MS5611.getAltitudeFt(temperatureF, pressurePa), 
            samplesPerSec, 
            ALTITUDE_FILTER_DURATION
          );
        }
        else{
          altitudeFt = MS5611.getAltitudeFt(temperatureF, pressurePa);
        }

        //VERTICAL SPEED:
        if(millis()>6000){
          if(VSPEED_FILTER_DURATION){
            velocityFtPerSec = FILTER3.RUNNING_AVERAGE(
              MS5611.getVelocityFtPerSec(altitudeFt, millis()), 
              samplesPerSec, 
              VSPEED_FILTER_DURATION
            );
          }
          else{
            velocityFtPerSec = MS5611.getVelocityFtPerSec(altitudeFt, millis());
          }
        }
        else{velocityFtPerSec=0;}

        //DEBUG:
        //Serial.println(temperatureF); 
        //Serial.println(pressurePa);
        //Serial.println(altitudeFt); 
        //Serial.print(" "); 
        //Serial.println(velocityFtPerSec);     



        if(millis()>6000){
          BEEP.basedOnVelocity(altitudeFt, velocityFtPerSec, millis());
        }


  
      //====NOKIA5110=================================================================/

  SPI.begin();  //TODO -- FIND OUT WHY THE LCD WON'T RESPOND WITHOUT SPI.begin() EVERY LOOP;

  display.clearDisplay();

  //TEMPERATURE:
  display.setTextSize(1);
  display.setTextColor(BLACK);
  display.setCursor(0,40);
  //display.print(samplesPerSec);
  display.print(temperatureF,0);
  display.print("F");

  //VELOCITY:
  display.setTextSize(2);
  if(velocityFtPerSec>=10 || velocityFtPerSec<0){display.setCursor(58,34);}
  else if(velocityFtPerSec>=0){display.setCursor(70,34);}
  if(velocityFtPerSec<=-10){display.setCursor(46,34);}
  //display.setTextColor(BLACK); // 'inverted' text
  display.print(contrast,0);

  //ALTITUDE:
  display.setCursor(0,0); 
  if(altitudeFt>=10000){display.setTextSize(2);}
  else{display.setTextSize(3);}
  //display.setTextColor(WHITE, BLACK);
  display.print(altitudeFt,0);
  
  display.display();
  //delay(1);


      //====BUTTONS=================================================================/

        //Serial.print(" up:"); 
        //Serial.print(analogRead(VOL_UP));
        //Serial.print(" "); 
        //Serial.println(analogRead(VOL_DOWN));
        Serial.print(analogRead(BUTTON_UP)); Serial.print(" ");
        if(analogRead(BUTTON_UP)<100 && millis()-volMillis>=volDelay){
          volMillis = millis();
          volume+=2;
          adjustVolumeTo(volume);
          tone(BEEP_PIN, 400, 100);
        }

        Serial.print(analogRead(BUTTON_DOWN)); Serial.print(" ");
        if(analogRead(BUTTON_DOWN)<100 && millis()-volMillis>=volDelay){
          volMillis = millis();
          volume-=2;
          adjustVolumeTo(volume);
          tone(BEEP_PIN, 400, 100);
        }

        Serial.print(analogRead(BUTTON_SELECT)); Serial.println(" ");
        if(analogRead(BUTTON_SELECT)<100){
          //Serial.println("SELECT");
          tone(BEEP_PIN, 400, 100);
        }
  

}









//v^SPEEEEEEEEEEEEEEEEEEEEEEEEEEEEEEEEEEEEEEEEEEEEEEEEEEEEEEEEEEEEEEEEEEEEEEEEEEED    
//                                                                              //
//                            DIGITAL VOLUME CONTROL                            //
//                                                                              //
//v^SPEEEEEEEEEEEEEEEEEEEEEEEEEEEEEEEEEEEEEEEEEEEEEEEEEEEEEEEEEEEEEEEEEEEEEEEEEEED
void adjustVolumeTo(int volLevel){
  
  // take the SS pin low to select the chip:
  digitalWrite(POT_CS, LOW);
  
  //  send in the address and value via SPI:
  int address = 0;
  SPI.transfer(address);
  SPI.transfer(volLevel);
  
  // take the SS pin high to de-select the chip:
  digitalWrite(POT_CS, HIGH);
}

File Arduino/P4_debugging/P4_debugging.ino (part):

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
#define BAUD_RATE                 115200    // Serial Monitor baud rate
#define POWER_PIN                     A0    // DEVICE POWERS OFF IF THIS PIN GOES LOW;
#define MS5611_CSB                    13    // Chip/Slave Select Pin
#define D1_OSR                         5    // (Default pressure OSR mode 5) 
#define D2_OSR                         2    // (Default temperature OSR mode 2) 
/*#define EPD_CS                         6
#define EPD_DC                        10
#define EPD_RST                       11
#define EPD_BUSY                      12*/
#define PRESSURE_FILTER_DURATION       0    // (AVERAGING DURATION: 1ms to 2000ms)
#define ALTITUDE_FILTER_DURATION    1000    // (AVERAGING DURATION: 1ms to 2000ms)
#define VSPEED_FILTER_DURATION      1000    // (AVERAGING DURATION: 1ms to 2000ms)
#define TEMPERATURE_FILTER_DURATION    0    // (AVERAGING DURATION: 1ms to 2000ms)
#define POT_CS                        A3
#define BEEP_PIN                      A5    // (Default A5) Pin connected to buzzer 
#define BUTTON_PIN                    A1    // CONNECT THE OTHER BUTTON LEAD TO 3.3V;


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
